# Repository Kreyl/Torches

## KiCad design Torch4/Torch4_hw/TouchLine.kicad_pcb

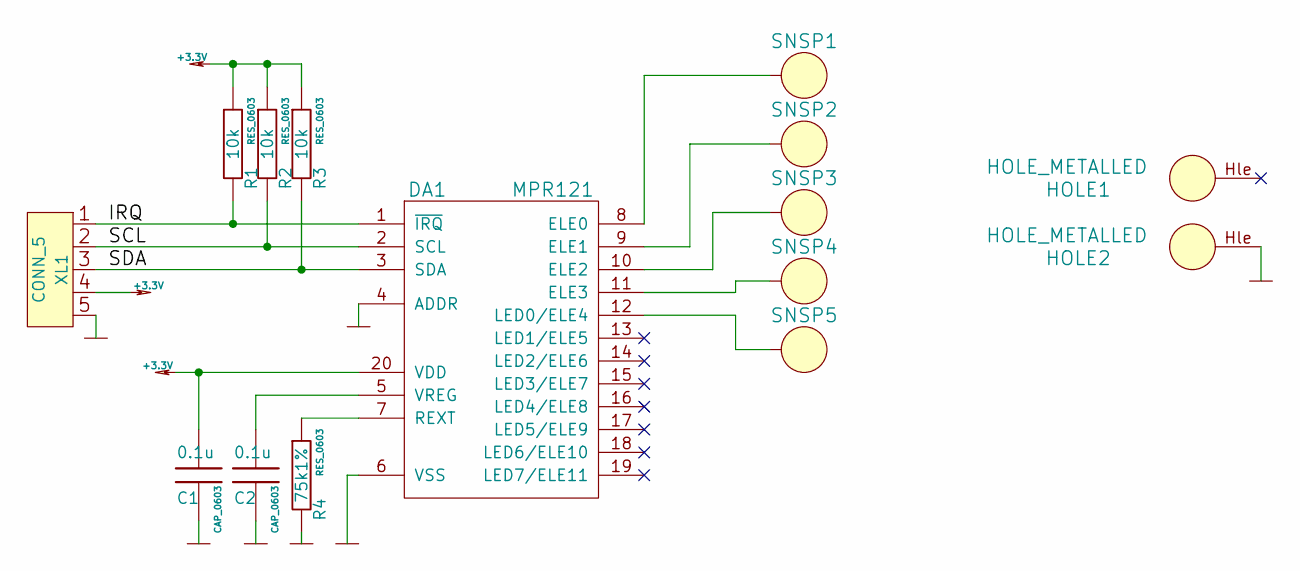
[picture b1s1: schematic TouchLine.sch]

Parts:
C1, C2: 0.1u; CAP_0603
DA1: MPR121
HOLE1, HOLE2: HOLE_METALLED
R1, R2, R3: 10k; RES_0603
R4: 75k1%; RES_0603
SNSP1, SNSP2, SNSP3, SNSP4, SNSP5: SENSORPAD
XL1: CONN_5

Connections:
+3.3V: C1.1, DA1.20 (VDD), R1.1, R2.1, R3.1, XL1.4
/IRQ: DA1.1 (~IRQ), R1.2, XL1.1
/SCL: DA1.2 (SCL), R2.2, XL1.2
/SDA: DA1.3 (SDA), R3.2, XL1.3
GND: C1.2, C2.2, DA1.4 (ADDR), DA1.6 (VSS), HOLE2.Hle, R4.2, XL1.5
unnamed: C2.1, DA1.5 (VREG)
unnamed: DA1.7 (REXT), R4.1
unnamed: DA1.8 (ELE0), SNSP1.1
unnamed: DA1.9 (ELE1), SNSP2.1
unnamed: DA1.10 (ELE2), SNSP3.1
unnamed: DA1.12 (LED0/ELE4), SNSP5.1
unnamed: DA1.11 (ELE3), SNSP4.1

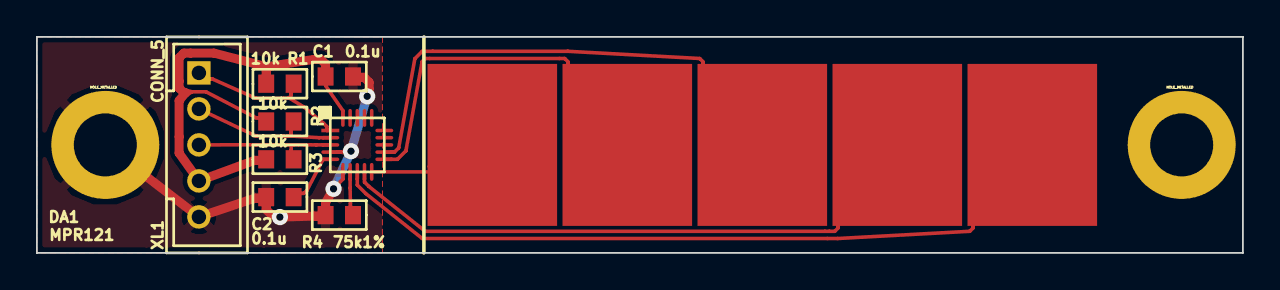
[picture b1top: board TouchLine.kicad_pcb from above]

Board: 2 copper layers, 67.0 x 12.0 mm, 15 parts (0 on the bottom side), 12 nets.

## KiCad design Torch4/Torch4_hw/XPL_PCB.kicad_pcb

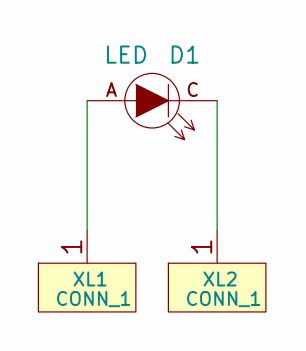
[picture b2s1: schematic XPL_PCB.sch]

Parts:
D1: LED
XL1, XL2: CONN_1

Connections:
unnamed: D1.A, XL1.1
unnamed: D1.C, XL2.1

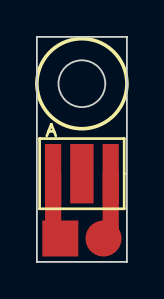
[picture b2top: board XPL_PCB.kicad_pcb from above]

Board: 2 copper layers, 5.0 x 12.5 mm, 3 parts (0 on the bottom side), 2 nets.

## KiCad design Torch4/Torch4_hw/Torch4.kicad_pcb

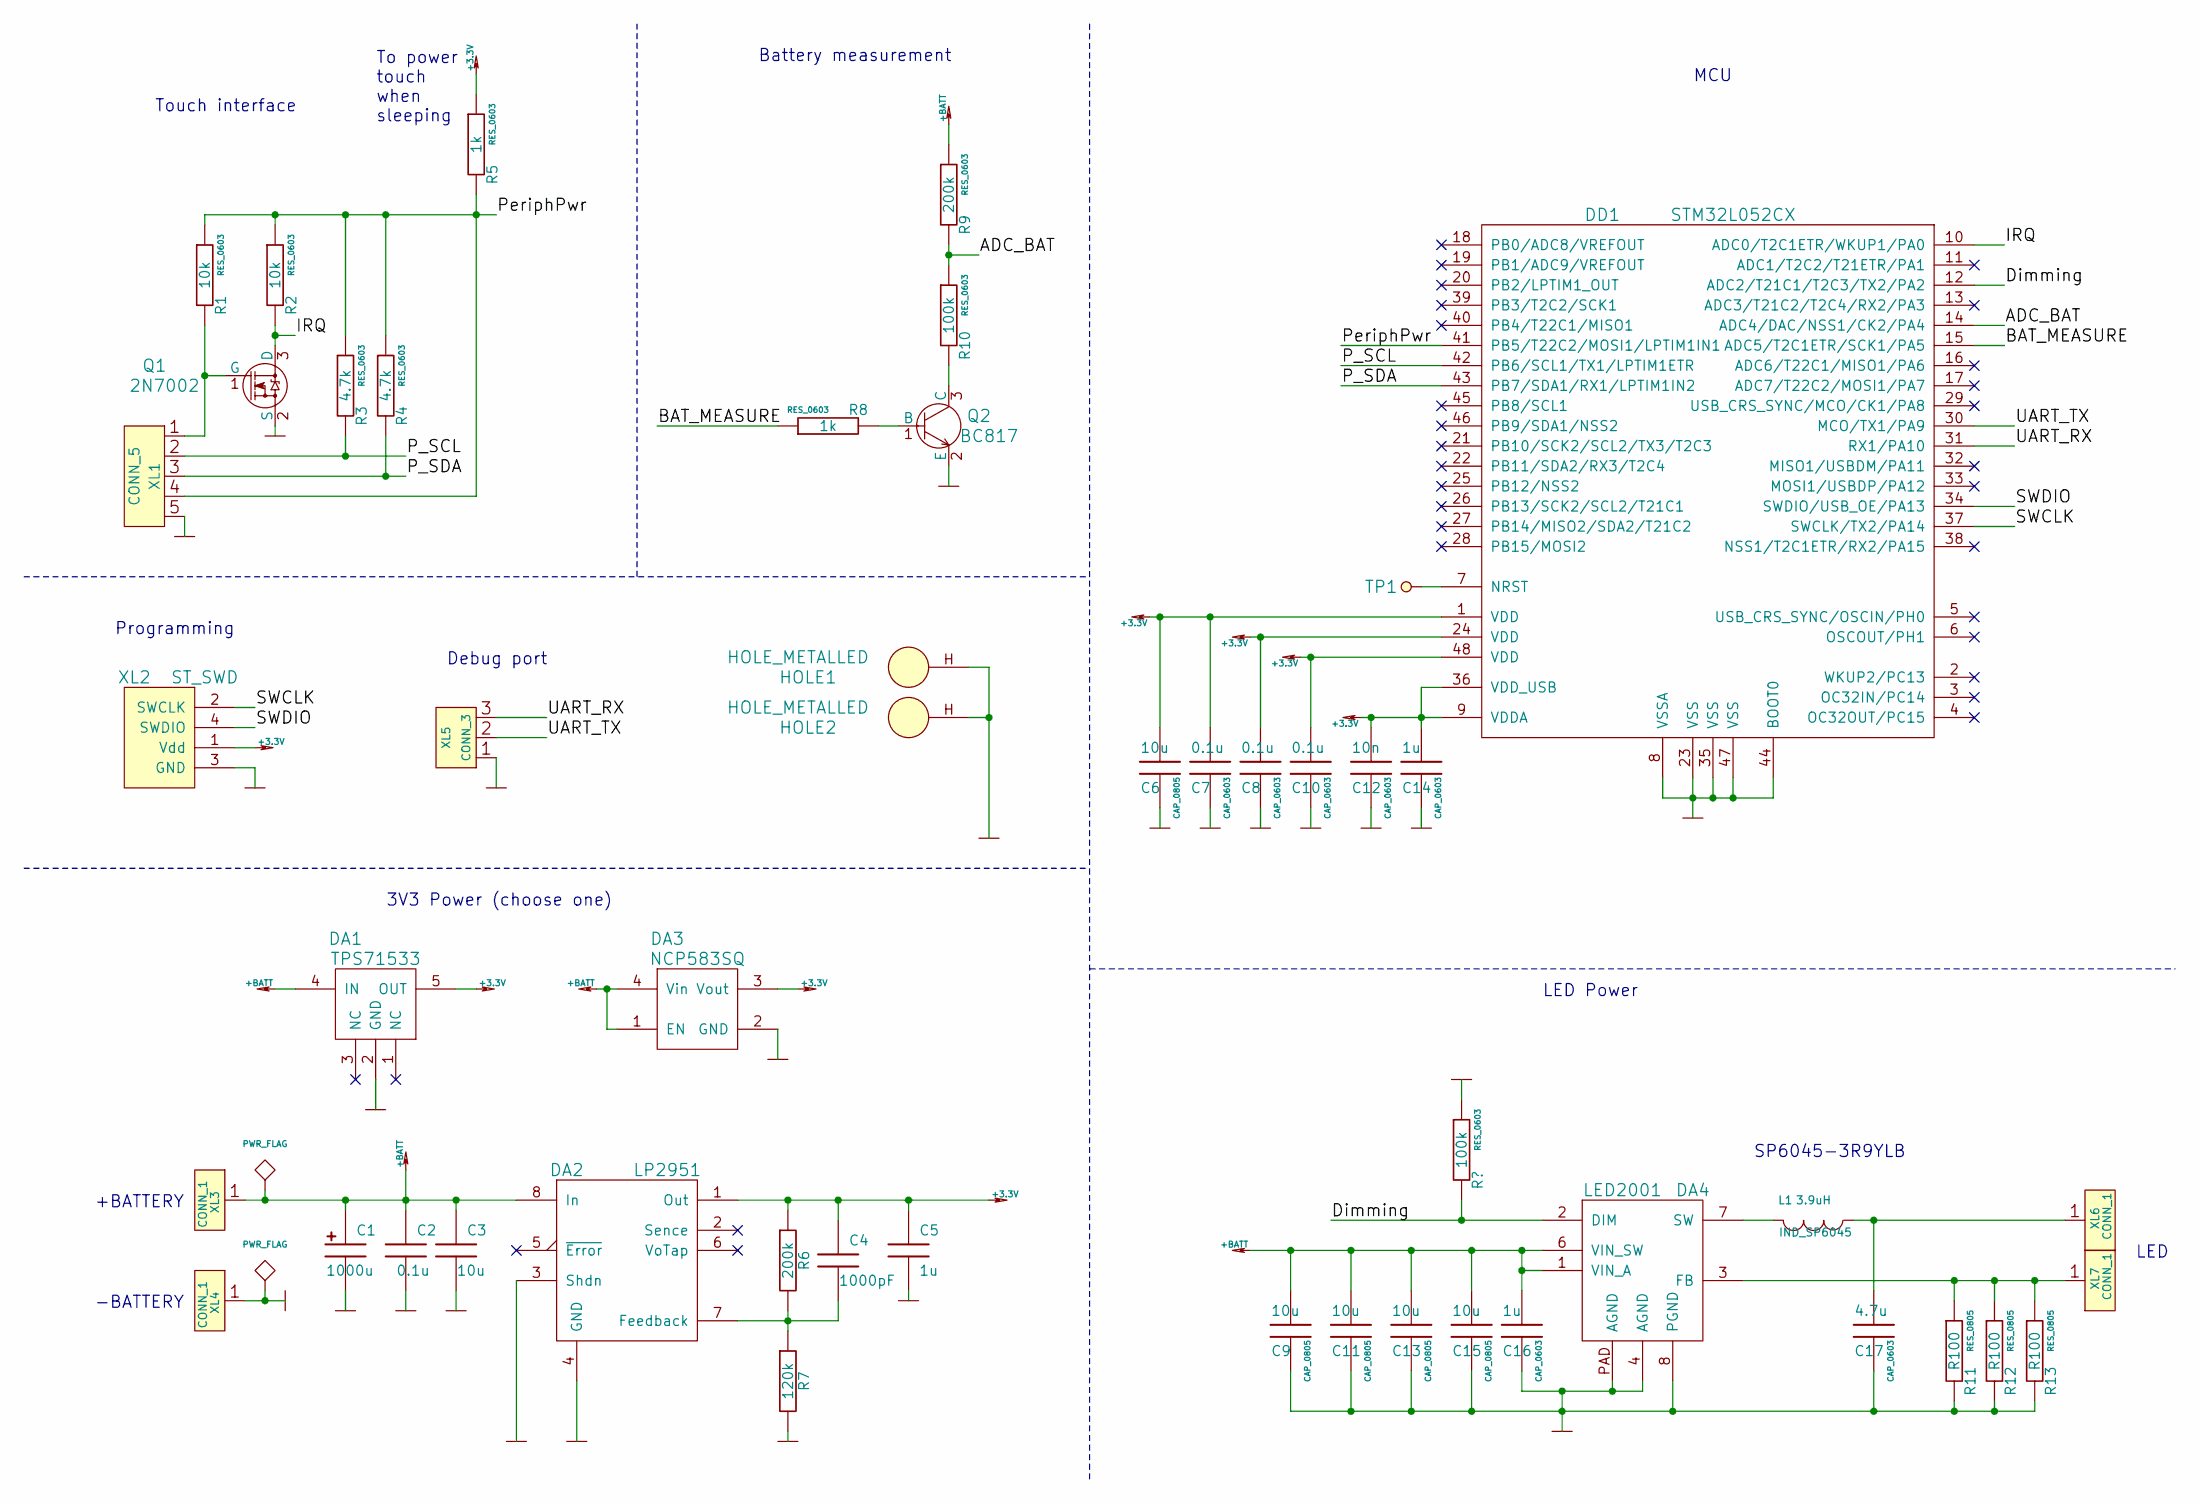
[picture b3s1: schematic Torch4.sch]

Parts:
C1: 1000u
C2: 0.1u
C3: 10u
C4: 1000pF
C5: 1u
C6, C9, C11, C13, C15: 10u; CAP_0805
C7, C8, C10: 0.1u; CAP_0603
C12: 10n; CAP_0603
C14, C16: 1u; CAP_0603
C17: 4.7u; CAP_0603
DA1: TPS71533
DA2: LP2951
DA3: NCP583SQ
DA4: LED2001
DD1: STM32L052CX
HOLE1, HOLE2: HOLE_METALLED
L1: 3.9uH; IND_SP6045
Q1: 2N7002
Q2: BC817
R1, R2: 10k; RES_0603
R3, R4: 4.7k; RES_0603
R5, R8: 1k; RES_0603
R6: 200k
R7: 120k
R9: 200k; RES_0603
R10: 100k; RES_0603
R11, R12, R13: R100; RES_0805
TP1: TESTPOINT
XL1: CONN_5
XL2: ST_SWD
XL3, XL4: CONN_1
XL5: CONN_3
XL6, XL7: CONN_1

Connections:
+3.3V: C4.1, C5.1, C6.1, C7.1, C8.1, C10.1, C12.1, C14.1, DA1.5 (OUT), DA2.1 (Out), DA3.3 (Vout), DD1.1 (VDD), DD1.9 (VDDA), DD1.24 (VDD), DD1.36 (VDD_USB), DD1.48 (VDD), R5.1, R6.1, XL2.1 (Vdd)
+BATT: C1.1, C2.1, C3.1, C9.1, C11.1, C13.1, C15.1, C16.1, DA1.4 (IN), DA2.8 (In), DA3.1 (EN), DA3.4 (Vin), DA4.1 (VIN_A), DA4.6 (VIN_SW), R9.1, XL3.1
/ADC_BAT: DD1.14 (ADC4/DAC/NSS1/CK2/PA4), R9.2, R10.1
/BAT_MEASURE: DD1.15 (ADC5/T2C1ETR/SCK1/PA5), R8.1
/Dimming: DA4.2 (DIM), DD1.12 (ADC2/T21C1/T2C3/TX2/PA2)
/IRQ: DD1.10 (ADC0/T2C1ETR/WKUP1/PA0), Q1.3 (D), R2.2
/P_SCL: DD1.42 (PB6/SCL1/TX1/LPTIM1ETR), R3.2, XL1.2
/P_SDA: DD1.43 (PB7/SDA1/RX1/LPTIM1IN2), R4.2, XL1.3
/PeriphPwr: DD1.41 (PB5/T22C2/MOSI1/LPTIM1IN1), R1.1, R2.1, R3.1, R4.1, R5.2, XL1.4
/SWCLK: DD1.37 (SWCLK/TX2/PA14), XL2.2 (SWCLK)
/SWDIO: DD1.34 (SWDIO/USB_OE/PA13), XL2.4 (SWDIO)
/UART_RX: DD1.31 (RX1/PA10), XL5.3
/UART_TX: DD1.30 (MCO/TX1/PA9), XL5.2 (PM)
GND: C1.2, C2.2, C3.2, C5.2, C6.2, C7.2, C8.2, C9.2, C10.2, C11.2, C12.2, C13.2, C14.2, C15.2, C16.2, C17.2, DA1.2 (GND), DA2.3 (Shdn), DA2.4 (GND), DA3.2 (GND), DA4.4 (AGND), DA4.8 (PGND), DA4.PAD (AGND), DD1.8 (VSSA), DD1.23 (VSS), DD1.35 (VSS), DD1.44 (BOOT0), DD1.47 (VSS), HOLE1.H, HOLE1.Hle, HOLE2.H, HOLE2.Hle, Q1.2 (S), Q2.2 (E), R7.2, R11.2, R12.2, R13.2, XL1.5, XL2.3 (GND), XL4.1, XL5.1
unnamed: Q2.1 (B), R8.2
unnamed: Q2.3 (C), R10.2
unnamed: Q1.1 (G), R1.2, XL1.1
unnamed: C4.2, DA2.7 (Feedback), R6.2, R7.1
unnamed: DD1.7 (NRST), TP1.1
unnamed: DA4.7 (SW), L1.2
unnamed: DA4.3 (FB), R11.1, R12.1, R13.1, XL7.1
unnamed: C17.1, L1.1, XL6.1

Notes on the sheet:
Debug port
Programming
Touch interface
SP6045-3R9YLB
LED
To power touch when sleeping
-BATTERY
+BATTERY
MCU
Battery measurement
LED Power
3V3 Power (choose one)

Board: 2 copper layers, 48 parts (0 on the bottom side), 22 nets, no tracks yet.

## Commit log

2015-07-04 + Torches 1-3-4 added + Torch3 firmware Release Candidate
